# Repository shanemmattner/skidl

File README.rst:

===============================
skidl
===============================

.. image:: https://img.shields.io/pypi/v/skidl.svg
        :target: https://pypi.python.org/pypi/skidl

The SKiDL Python package lets you compactly describe the interconnection of 
electronic circuits and components.
The resulting Python program performs electrical rules checking
for common mistakes and outputs a netlist that serves as input to
a PCB layout tool.

* Free software: MIT license
* Documentation: http://devbisme.github.io/skidl
* User Forum: https://github.com/devbisme/skidl/discussions

Features
--------

* Has a powerful, flexible syntax (because it *is* Python).
* Permits compact descriptions of electronic circuits (think about *not* tracing
  signals through a multi-page schematic).
* Allows textual descriptions of electronic circuits (think about using 
  ``diff`` and `git <https://en.wikipedia.org/wiki/Git_(software)>`_ for circuits).
* Performs electrical rules checking (ERC) for common mistakes (e.g., unconnected device I/O pins).
* Supports linear / hierarchical / mixed descriptions of electronic designs.
* Fosters design reuse (think about using `PyPi <https://pypi.org/>`_ and `Github <https://github.com/>`_
  to distribute electronic designs).
* Makes possible the creation of *smart circuit modules* whose behavior / structure are changed parametrically
  (think about filters whose component values are automatically adjusted based on your
  desired cutoff frequency).
* Can work with any ECAD tool (only two methods are needed: one for reading the part libraries and another
  for outputing the correct netlist format).
* Can perform SPICE simulations (Python 3 only).
* Takes advantage of all the benefits of the Python ecosystem (because it *is* Python).

As a very simple example (see more in the 
`blog <https://devbisme.github.io/skidl/category/posts.html>`_),
the SKiDL program below describes a 
`two-input AND gate <https://raw.githubusercontent.com/nturley/netlistsvg/master/doc/and.svg?sanitize=true>`_
built from discrete transistors:

.. image:: https://raw.githubusercontent.com/nturley/netlistsvg/master/doc/and.svg?sanitize=true

.. code-block:: python

    from skidl import *

    # Create part templates.
    q = Part("Device", "Q_PNP_CBE", dest=TEMPLATE)
    r = Part("Device", "R", dest=TEMPLATE)

    # Create nets.
    gnd, vcc = Net("GND"), Net("VCC")
    a, b, a_and_b = Net("A"), Net("B"), Net("A_AND_B")

    # Instantiate parts.
    gndt = Part("power", "GND")             # Ground terminal.
    vcct = Part("power", "VCC")             # Power terminal.
    q1, q2 = q(2)                           # Two transistors.
    r1, r2, r3, r4, r5 = r(5, value="10K")  # Five 10K resistors.

    # Make connections between parts.
    a & r1 & q1["B C"] & r4 & q2["B C"] & a_and_b & r5 & gnd
    b & r2 & q1["B"]
    q1["C"] & r3 & gnd
    vcc += q1["E"], q2["E"], vcct
    gnd += gndt

    generate_netlist(tool=KICAD8) # Create KICAD version 8 netlist.

And this is the output that can be fed to a program like KiCad's ``PCBNEW`` to
create the physical PCB::

  (export (version D)
    (design
      (source "/home/devb/projects/KiCad/tools/skidl/tests/examples/svg/simple_and_gate.py")
      (date "07/19/2024 05:54 AM")
      (tool "SKiDL (1.2.2)"))
    (components
      (comp (ref #PWR1)
        (value GND)
        (footprint )
        (fields
          (field (name F0) #PWR)
          (field (name F1) GND))
        (libsource (lib power) (part GND))
        (sheetpath (names /top/18388231966295430075) (tstamps /top/18388231966295430075)))
      (comp (ref #PWR2)
        (value VCC)
        (footprint )
        (fields
          (field (name F0) #PWR)
          (field (name F1) VCC))
        (libsource (lib power) (part VCC))
        (sheetpath (names /top/12673122245445984714) (tstamps /top/12673122245445984714)))
      (comp (ref Q1)
        (value Q_PNP_CBE)
        (footprint )
        (fields
          (field (name F0) Q)
          (field (name F1) Q_PNP_CBE))
        (libsource (lib Device) (part Q_PNP_CBE))
        (sheetpath (names /top/5884947020177711792) (tstamps /top/5884947020177711792)))
      (comp (ref Q2)
        (value Q_PNP_CBE)
        (footprint )
        (fields
          (field (name F0) Q)
          (field (name F1) Q_PNP_CBE))
        (libsource (lib Device) (part Q_PNP_CBE))
        (sheetpath (names /top/12871193304116279102) (tstamps /top/12871193304116279102)))
      (comp (ref R1)
        (value 10K)
        (footprint )
        (fields
          (field (name F0) R)
          (field (name F1) R))
        (libsource (lib Device) (part R))
        (sheetpath (names /top/17200003438453088695) (tstamps /top/17200003438453088695)))
      (comp (ref R2)
        (value 10K)
        (footprint )
        (fields
          (field (name F0) R)
          (field (name F1) R))
        (libsource (lib Device) (part R))
        (sheetpath (names /top/12314015795656540138) (tstamps /top/12314015795656540138)))
      (comp (ref R3)
        (value 10K)
        (footprint )
        (fields
          (field (name F0) R)
          (field (name F1) R))
        (libsource (lib Device) (part R))
        (sheetpath (names /top/11448722674936198910) (tstamps /top/11448722674936198910)))
      (comp (ref R4)
        (value 10K)
        (footprint )
        (fields
          (field (name F0) R)
          (field (name F1) R))
        (libsource (lib Device) (part R))
        (sheetpath (names /top/2224275500810828611) (tstamps /top/2224275500810828611)))
      (comp (ref R5)
        (value 10K)
        (footprint )
        (fields
          (field (name F0) R)
          (field (name F1) R))
        (libsource (lib Device) (part R))
        (sheetpath (names /top/3631169005149914336) (tstamps /top/3631169005149914336))))
    (nets
      (net (code 1) (name A)
        (node (ref R1) (pin 1)))
      (net (code 2) (name A_AND_B)
        (node (ref Q2) (pin 1))
        (node (ref R5) (pin 1)))
      (net (code 3) (name B)
        (node (ref R2) (pin 1)))
      (net (code 4) (name GND)
        (node (ref #PWR1) (pin 1))
        (node (ref R3) (pin 2))
        (node (ref R5) (pin 2)))
      (net (code 5) (name N$1)
        (node (ref Q1) (pin 2))
        (node (ref R1) (pin 2))
        (node (ref R2) (pin 2)))
      (net (code 6) (name N$2)
        (node (ref Q1) (pin 1))
        (node (ref R3) (pin 1))
        (node (ref R4) (pin 1)))
      (net (code 7) (name N$3)
        (node (ref Q2) (pin 2))
        (node (ref R4) (pin 2)))
      (net (code 8) (name VCC)
        (node (ref #PWR2) (pin 1))
        (node (ref Q1) (pin 3))
        (node (ref Q2) (pin 3))))
  )

## Note
Note: to generate PCB require you to run the python installed with Kicad.  For Mac that is at
/Applications/KiCad/KiCad.app/Contents/Frameworks/Python.framework/Versions/Current/bin/python3

So to run this script you would do:
/Applications/KiCad/KiCad.app/Contents/Frameworks/Python.framework/Versions/Current/bin/python3 skidl_llm_test.py
This will generate a netlist file and a pcb file in the same directory as this script

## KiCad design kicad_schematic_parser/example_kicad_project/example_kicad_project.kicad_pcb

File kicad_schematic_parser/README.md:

# SKiDL KiCad Schematic Parser

A Python module for SKiDL that parses and analyzes KiCad schematic files, converting them to SKiDL Python code. This module operates in two stages:
1. KiCad Schematic to Text: Extracts comprehensive information about components, pins, connections, and labels from KiCad schematics
2. Text to SKiDL: Converts the extracted information into SKiDL Python code for circuit definition

## Current Status

### KiCad to Text (Complete)
- ✅ Component extraction with detailed properties
- ✅ Pin position calculation with support for rotated components
- ✅ Wire connection analysis
- ✅ Label parsing (local, hierarchical, and power labels)
- ✅ Net connectivity analysis
- ✅ Support for hierarchical sheets

### Text to SKiDL (In Progress)
- ✅ Component parsing
- 🚧 Pin and connection parsing (Planned)
- 🚧 Net parsing (Planned)
- 🚧 Sheet structure parsing (Planned)
- 🚧 Circuit hierarchy building (Planned)
- 🚧 SKiDL code generation (Planned)

## Usage

The tool supports two modes of operation:

### 1. KiCad to Text Conversion
```bash
python src/main.py --mode kicad2text <schematic_file_path>
```

This will analyze the schematic and output a text file containing:
- Component list with properties
- Pin details including positions and types
- Wire connections
- Label information (local, hierarchical, power)
- Complete netlist showing connectivity

### 2. Text to SKiDL Conversion (Coming Soon)
```bash
python src/main.py --mode text2skidl <text_file_path>
```

This will convert the text representation into SKiDL Python code.

## Project Structure

```
src/
├── main.py                     # Main entry point with dual mode support
├── kicad_hierarchy_parser/     # KiCad to Text conversion
│   ├── parser.py              # Main parser functionality
│   ├── components/            # Component parsing
│   │   └── component_parser.py
│   ├── connectivity/          # Wire and net analysis
│   │   ├── wire_parser.py
│   │   └── net_parser.py
│   ├── labels/                # Label parsing
│   │   └── label_parser.py
│   └── utils/                 # Utility functions
│       └── geometry.py
└── skidl_generator/           # Text to SKiDL conversion
    ├── component_parser/      # Phase 1: Parse component information
    ├── pin_parser/           # Phase 2: Parse pin information
    ├── net_parser/           # Phase 3: Parse net information
    ├── sheet_parser/         # Phase 4: Parse sheet structure
    ├── hierarchy_builder/    # Phase 5: Build circuit hierarchy
    └── code_generator/       # Phase 6: Generate SKiDL code
```

## Known Bugs

### KiCad to Text
- Labels placed in the middle of a wire do not always get detected
- Labels might not transfer when connected
  - ie 5v connected to label1, then label1 connected to label2. label2 might not be connected to 5v

## Development

The project is organized into two main modules:

### KiCad Hierarchy Parser
- Handles KiCad schematic file parsing
- Extracts component and pin information
- Analyzes wire connections and nets
- Processes different types of schematic labels

### SKiDL Generator
- Converts text representation to SKiDL code
- Follows modular approach with separate parsers
- Handles component properties and connections
- Manages circuit hierarchy and sheet structure

### Running Tests

Tests are located in `src/kicad_parser/tests`. To run the tests:

1. Install pytest if you haven't already:
```bash
pip install pytest
```

2. Run tests from the project root:
```bash
pytest
```

The test suite includes:

Pin Placement Tests:
- Component pin position calculations
- Support for rotated components
- Pin electrical type verification
- Tests using power supplies, resistor dividers, and microcontroller schematics

Wire Connection Tests:
- Wire connectivity analysis
- Net detection and verification
- Power and ground connections
- Local and hierarchical label connections
- Tests using voltage monitoring and power supply circuits

## Dependencies

- Python 3.6+
- SKiDL (for circuit definition in code)
- kiutils (for KiCad schematic file parsing)

## Integration with SKiDL

This module is designed to be integrated with SKiDL, a Python package that allows you to define electronic circuits using Python code. The parser extracts KiCad schematic information that can be used to:

1. Create SKiDL Circuit objects from existing KiCad schematics
2. Convert between SKiDL and KiCad representations
3. Enable hybrid workflows combining code-defined and schematic-captured circuits

For more information about SKiDL, visit: [SKiDL Documentation](https://xesscorp.github.io/skidl/docs/_site/)

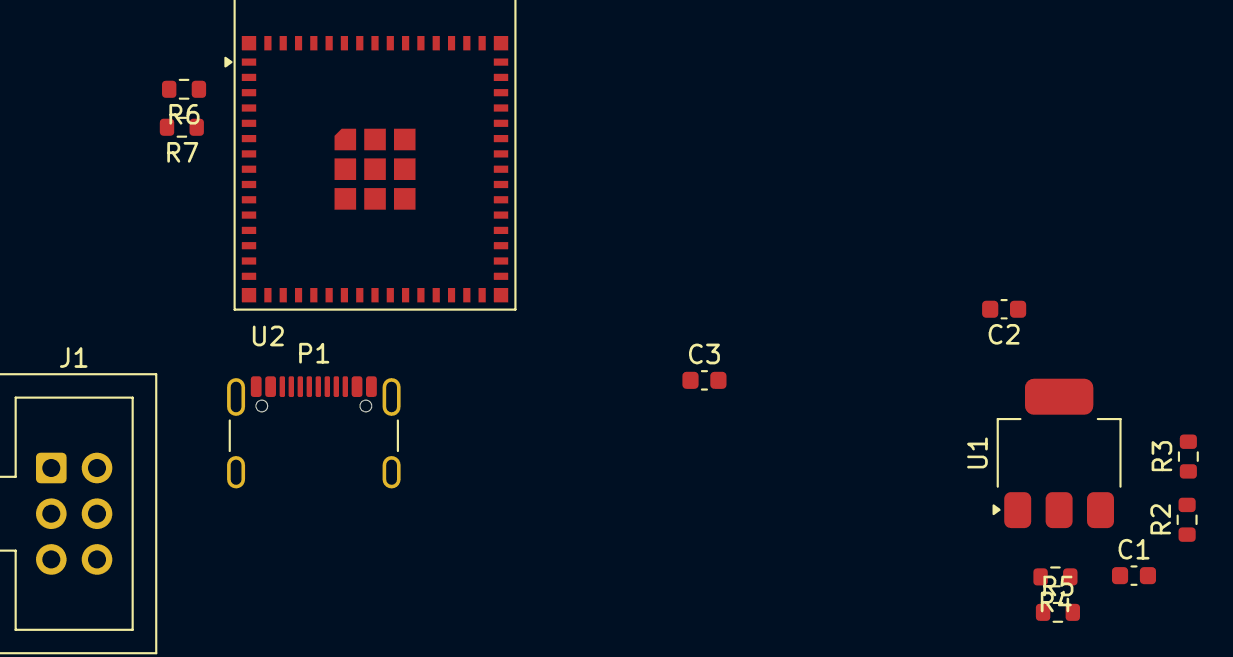
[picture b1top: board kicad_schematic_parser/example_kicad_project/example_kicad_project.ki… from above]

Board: 2 copper layers, 14 parts (1 on the bottom side), 12 nets, no tracks yet.

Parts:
C1, C2: 10uF; C_0603_1608Metric
C3: 100nF; C_0603_1608Metric
J1: Conn_02x03_Odd_Even; IDC-Header_2x03_P2.54mm_Vertical
P1: USB_C_Plug_USB2.0; USB_C_Receptacle_GCT_USB4105-xx-A_16P_TopMnt_Horizontal
R1: 5.1K; R_0603_1608Metric
R2, R4, R6: 2K; R_0603_1608Metric
R3, R5, R7: 1K; R_0603_1608Metric
U1: NCP1117-3.3_SOT223; SOT-223-3_TabPin2
U2: ESP32-S3-MINI-1; ESP32-S2-MINI-1

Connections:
3.3V: C2.1, C3.1, J1.2, R4.1, R6.1, U1.2, U2.3
3v3_monitor: R4.2, R5.1, U2.7
5v_monitor: R2.2, R3.1, U2.6
D+: P1.A6, U2.24
D-: P1.A7, U2.23
GND: C1.2, C2.2, C3.2, J1.4, J1.6, P1.A1, P1.A12, P1.B1, P1.B12, P1.S1, R1.2, R3.2, R5.2, R7.2, U1.1, U2.1, U2.2, U2.42, U2.43, U2.46, U2.47, U2.48, U2.49, U2.50, U2.51, U2.52, U2.53, U2.54, U2.55, U2.56, U2.57, U2.58, U2.59, U2.60, U2.61, U2.62, U2.63, U2.64, U2.65
HW_VER: R6.2, R7.1, U2.5
unnamed: P1.A5, R1.1
unnamed: J1.1, U2.45
unnamed: J1.3, U2.39
unnamed: J1.5, U2.4
VBUS_1: C1.1, P1.A4, P1.A9, P1.B4, P1.B9, R2.1, U1.3

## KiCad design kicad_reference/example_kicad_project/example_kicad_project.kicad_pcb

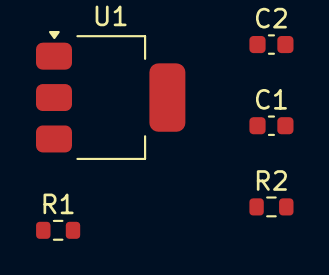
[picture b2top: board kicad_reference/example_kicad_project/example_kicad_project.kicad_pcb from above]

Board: 2 copper layers, 5 parts (0 on the bottom side), 3 nets, no tracks yet.

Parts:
C1, C2: 10uF; C_0603_1608Metric
R1, R2: 1K; R_0603_1608Metric
U1: NCP1117-3.3_SOT223; SOT-223-3_TabPin2

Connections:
+3V3: C1.1, U1.2
GND_2: C1.2, C2.2, U1.1
R1_2-R2_1: C2.1, R1.1, R2.2, U1.3

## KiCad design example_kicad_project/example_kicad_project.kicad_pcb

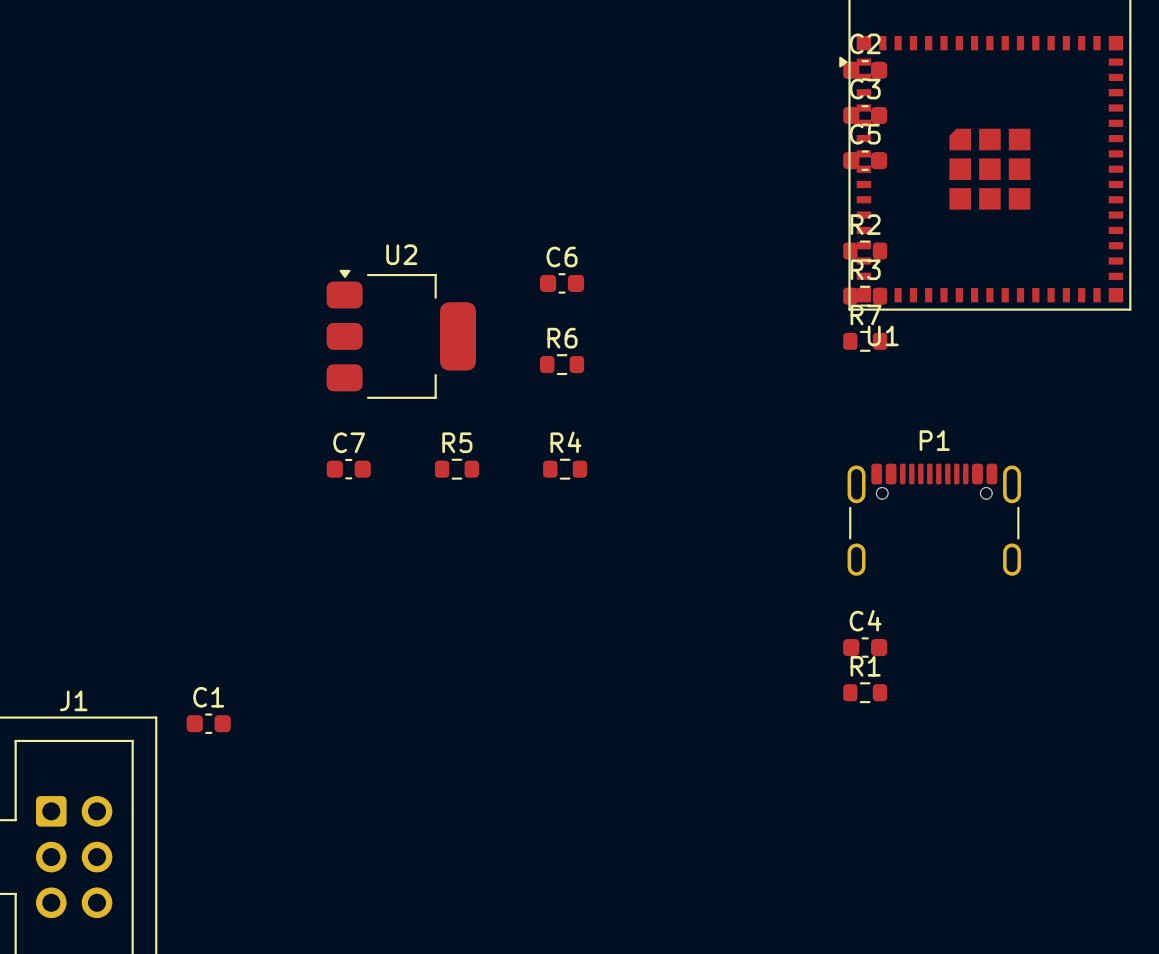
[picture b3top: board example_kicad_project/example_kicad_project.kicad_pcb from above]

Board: 2 copper layers, 18 parts (0 on the bottom side), 13 nets, no tracks yet.

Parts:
C1, C5, C6: 100nF; C_0603_1608Metric
C2, C3, C4, C7: 10uF; C_0603_1608Metric
J1: Conn_02x03_Odd_Even; IDC-Header_2x03_P2.54mm_Vertical
P1: USB_C_Plug_USB2.0; USB_C_Receptacle_GCT_USB4105-xx-A_16P_TopMnt_Horizontal
R1, R4, R5: 1k; R_0603_1608Metric
R2, R3, R6: 2k; R_0603_1608Metric
R7: 5.1K; R_0603_1608Metric
U1: ESP32-S3-MINI-1; ESP32-S2-MINI-1
U2: NCP1117-3.3_SOT223; SOT-223-3_TabPin2

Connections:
3v3_monitor: C5.1, R4.1, R6.2, U1.6
5v_monitor: C6.1, R3.2, R5.1, U1.7
+3V3: C2.1, C3.1, J1.2, R2.1, R6.1, U1.3, U2.2
+5V: C4.1, C7.1, P1.A4, P1.A9, P1.B4, P1.B9, R3.1, U2.3
D+: P1.A6, U1.24
D-: P1.A7, U1.23
GND: C1.2, C2.2, C3.2, C4.2, C5.2, C6.2, C7.2, J1.4, P1.A1, P1.A12, P1.B1, P1.B12, P1.S1, R1.2, R4.2, R5.2, R7.2, U1.1, U1.2, U1.42, U1.43, U1.46, U1.47, U1.48, U1.49, U1.50, U1.51, U1.52, U1.53, U1.54, U1.55, U1.56, U1.57, U1.58, U1.59, U1.60, U1.61, U1.62, U1.63, U1.64, U1.65, U2.1
unnamed: P1.A5, R7.1
esp32s3mini1/EN: J1.1, U1.45
esp32s3mini1/HW_VER: C1.1, R1.1, R2.2, U1.5
esp32s3mini1/IO0: J1.6, U1.4
esp32s3mini1/RX: J1.5, U1.40
esp32s3mini1/TX: J1.3, U1.39

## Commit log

2025-01-03 add scripts and docs for s-expressions and llm chat
2025-01-04 update llm script
2025-01-17 Add note about how to generate PCB with skidl
2025-01-17 working on schematic gen. maybe almost there?
2025-01-17 fix one error
2025-01-17 add documentation
2025-01-18 modified example to be hierarchical. add kicad_to_skidl script
2025-01-18 improved script
2025-01-18 refactor
2025-01-18 starting over slowly by making subcircuits
2025-01-18 script to find components and place them in skidl script somewhat working
2025-01-18 refactor logic
2025-01-18 working import?
2025-01-18 somewhat working schematic import
2025-01-18 update resistor divider
2025-01-18 adding existing logic
2025-01-18 updating logic to handle more circuits
2025-01-18 commit before changing more
2025-01-19 add somewhat working parser code
2025-01-19 working parser to rename nets based on labels
2025-01-19 combining labels kinda working
2025-01-20 combining labels sometimes working
2025-01-20 refactor code into modules, still working
2025-01-20 continuing to improve and refactor
2025-01-20 fixed some label connection issues, a few remain
2025-01-20 committing latest
2025-01-20 refactor, take out hard coded values
2025-01-20 simplify label testing. add errors to README.md
2025-01-20 add next steps section
2025-01-20 add tests for wire connections
2025-01-20 finding sheet information succesfully
2025-01-20 finding sheet pins
2025-01-20 now associating sheet with a pin
2025-01-20 logic seems to understand connections between sheets
2025-01-20 sheets detecting component connections to pins
2025-01-20 returning sub-sheets info
2025-01-20 add logic to recursively find subsheets and print out their info
2025-01-20 finding sub sheets recursively
2025-01-20 add formatting
2025-01-20 printing out parent sheet
2025-01-20 hierachries kinda merging?
2025-01-20 remove test with incomplete code for it
2025-01-20 fix error
2025-01-21 update script with new files
2025-01-21 working on hierachy connections
2025-01-21 shorten query
2025-01-21 change to esp32 project, make more practical
2025-01-21 adding file for making skidl circuit
2025-01-21 make plan for attach
2025-01-21 refactor development plan
2025-01-21 commiting all changes
2025-01-21 add component parser and tests
2025-01-21 parser succesfully finding parts in hierchy.txt
2025-01-22 passing unit tests with component parser
2025-01-22 remove unneeded folder
2025-01-22 add docs folder
2025-01-22 add example for using kiutils to generate and place a part
2025-01-22 rename folder
2025-01-22 refactor code
2025-01-22 make script to test parser logic
2025-01-22 update readme, update parsing logic
2025-01-22 working component parser again
2025-01-22 adding tests for net name parsing
2025-01-22 made failing tests
2025-01-23 updating context
2025-01-23 fix pin position parsing
2025-01-23 some tests now passing
2025-01-23 update context
2025-01-23 passing pin location test
2025-01-23 update context, remove hierachy test
2025-01-23 another test passing
2025-01-23 committing working tests
2025-01-23 all tests passing!
2025-01-23 refactor skidl generator
2025-01-23 component parser is working
2025-01-23 fixed duplicate reference parts
2025-01-23 remove duplicate code
2025-01-24 add readme info
2025-01-24 change name of output file
2025-01-24 add failing tests for skidl subcircuit generation
2025-01-24 new failing unit tests
2025-01-24 m 1 passing test?
2025-01-24 2 passing tests
2025-01-24 passing unit tests!
2025-01-25 passing tests
2025-01-25 updated hierarchy.txt
2025-01-25 add more examples to sheet parsing
2025-01-25 refactoring logic to pass tests
2025-01-25 starting new parser for kicad to skidl
2025-01-25 last commit
2025-01-25 modifying netlist to skidl logic
2025-01-25 add example netlists
2025-01-25 restor original logic
2025-01-25 refactoring netlist to skidl logic
2025-01-25 outputting directory
2025-01-25 generating valid skidl code from netlist
2025-01-25 generating multiple files now
2025-01-25 adding example outputs
2025-01-25 mostly working conversion
2025-01-25 mostly working code
2025-01-25 hierarchy schematics seem to be generating
2025-01-25 adding cline docs
2025-01-26 restor __init__ file accidentally overwritten
2025-01-26 fix net parsing?
2025-01-26 working logic
2025-01-26 add to planning doc
2025-01-26 seemingly working logic
2025-01-26 outputing correct circuit
2025-01-26 generate updated net file
2025-01-26 regenerated latest files
2025-01-26 updated documentation in prep for solving issues
2025-01-26 logic mostly working
2025-01-26 add example project to use
2025-01-26 add blank kicad project
2025-01-26 add blank kicad project to copy, add code to copy the blank project when generating a schematic
2025-01-26 remove top level blank kicad project
2025-01-26 add logic to copy files to correct directory
2025-01-26 generating files close to correct
2025-01-27 generating blank project and sub-files
2025-01-27 adding hiearchy sheets to top level kicad schematic
2025-01-27 hierarchical sheets generating correctly
2025-01-27 add cline docs to track project
2025-01-27 make separate function to extract part info
2025-01-27 add logic to add parts to schematics
2025-01-27 kinda working part gen
2025-01-27 edit logic to catch legalized name
2025-01-27 add logic for printing out part info
2025-01-28 somewhat working shcematic generation for some files
2025-01-28 making progress
2025-01-28 adding reference kicad docs
2025-01-28 working circuits besides esp32
2025-01-28 refactor schematic writer logic, almost working!
2025-01-29 adding peripheral files
2025-01-29 adding all changes from today, not working yet but it seems like a good strategy
2025-01-29 restructure files and folders to be more organized
2025-01-29 move files around, add tests
2025-01-29 code outputing schematics, but parts are not correct
2025-01-29 add tests files
2025-01-29 working unit test for blank schematic generation
2025-01-29 passing resistor test
2025-01-29 add tests
2025-01-29 passing the one resistor unit test
2025-01-30 some passing 2 resistor unit tests
2025-01-30 passing unit tests
2025-01-30 refactor unit test
2025-01-30 passing unit tests, edit some of the business logic
2025-01-30 made kicad project files align
2025-01-30 add tests for kicad project file generation
2025-01-30 add test for 4 resistors
2025-01-30 add footprint and value to resistors
2025-01-30 passing nesting hierarchy test
2025-01-30 non-functional code
2025-01-30 update docs on the current hierarchical issue
2025-01-30 broken code, making progress
2025-01-31 genering one resistor top sheet
2025-01-31 updating code that compiles before changing it
2025-01-31 generating a resistor now
2025-01-31 not working yet
2025-01-31 generating hierarchies, but not parts now
2025-01-31 generating hierarchical sschematics fine now. with parts!
2025-01-31 passing more unit tests
2025-01-31 working logic to generate hierarchical schematics
2025-01-31 add test for ncp117 nested part
2025-01-31 fix part placement and generation
2025-01-31 break up tests into 2 directories
2025-01-31 Refactor capacitor test to match resistor test structure
    - Renamed test function to test_schematic_generation
    - Added detailed docstring explaining test purpose
    - Used different project and directory names
    - Added explicit verification of both schematic files
    - Updated project directory path construction
2025-01-31 removed some tests
2025-01-31 refactor unit tests to follow working examples
